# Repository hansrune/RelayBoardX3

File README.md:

# Relay board X3

Work in progress / still a prototype...

A DYI 3x relay board based on ESP32c3. This is a multi purpose board used for:

- `Garage doors` - controlling dual garage doors and control use of external switches
- `Ventilator / 1-phase small motor` 1-2-3 speed control. 

This board is tested with ESPhome and ESPEasy [firmware](#firmwares) (build instructions below), and is easily used with home automation systems that support MQTT auto discovery, the native Home Assistant API, and the many [controllers that ESPEasy supports](https://espeasy.readthedocs.io/en/latest/Controller/_Controller.html)

## Introduction

Some of the main features and benefits

- **3x galvanic isolated relays**
- **Car precense sensors**
    - Ultrasound sensor option
- **I2C support**
    - An I2C pin header with power supply is available to use with I2C sensors
    - ... or you can use the same GPIO pins for any other purpose of your choise
- **WiFi based**
    - This is almost a must have for most home automation systems
    - OTA support
    - Configuration backup, restore and bulk updates.
- **Firmware of your choise**
    - ESPEasy with Domoticz over http. Device creation uses virtual sensors
    - ESPEasy with Domotics and Home Assistant via MQTT. Device creation uses a MQTT configuration text file.
    - ESPHome to Home Assistant via MQTT and auto discovery
    - ESPHome to Domoticz via MQTT and auto discovery
    - ... and as the hardware supports using both Arduino and ESP-IF development kits, almost any other firmware can be created.
- **Seed Studio XIAO ESP32C3**
    - This device is shielded and comes with an external IPX antenna connector
    - FCC and CE regulations approved

<!--
## Setup and mounting - perhaps add later
-->

## Indicators

Each of the four valve outputs has a LED indicator at the back of the PCB

- LED D11 will indicate low level input from the flow meter
- LED D1
  - no change indicates out of power, device death/freeze or other
  - a duty cycle 1:1 will indicate a reset is ongoing
<!--
  - will blink with a duty cycle 1-4 or 4-1 to indicate valve closed or open
-->

## Implementation and design

The schematic diagram is [available here](KiCad//RelayBoardX3-schema-2.0.pdf). The [KiCad EDA](https://www.kicad.org/) project is in the [same folder](./KiCad)

### GPIO pin usage

| PIN      | Capabilty          | Function                              |
|----------|--------------------|---------------------------------------|
| GPIO2    | Acticve low output | LED D8 - not used                     |
| GPIO3    | Input with pull-up | J7 pin 2                              |
| GPIO4    | Input with pull-up | J7 pin 1                              |
| GPIO5    | Active high output | Relay 1                               |
| GPIO6    | Active high output | Relay 2                               |
| GPIO7    | I2C pulled up      | SDL                                   |
| GPIO8    | I2C pulled up      | SDA                                   |
| GPIO9    | Active low out     | LED D8 - status                       |
| GPIO10   | Active high output | Relay 3                               |
| GPIO20   | RX / 1-wire        | Serial or 1-wire sensor or ultrasound |
| GPIO21   | TX / 1-wire        | Serial or 1-wire sensor or ultrasound |

## Hardware - getting started

This project uses my [KiCad-lib-ESP32 repository](https://github.com/hansrune/KiCad-lib-ESP32.git) as a [git submodule](https://www.git-scm.com/book/en/v2/Git-Tools-Submodules). To check this out, use the following:

```bash
git clone --recurse-submodules https://github.com/hansrune/RelayBoardX4.git 
```

### Materials used

This project uses the [Seed Studio XIAO ESP32C3 RISC-V module](https://www.seeedstudio.com/Seeed-XIAO-ESP32C3-p-5431.html). This tiny device has proven to be more reliable than most ESP8266 modules used in earlier versions. This module also comes with an IPX connector for connecting an external antenna, and is delivered with a simple external antenna for good range. This device is also EMI shielded and certified.

Any available 12V DC power supply delivering 500mA or more should do for the control board. You will need to add the total power draw for the relays

There are many options and possible pinouts for DC-DC converters for the 12V to 5V conversion. A linear regulator (L7805) will need a heatsink, so a DC-DC converter is recommended.

The MOSFETs need a low Vgs trigger voltage, i.e. well under 3V on full load. I have used Si2302/N025P for the N-channel, SOT-23 package.

Resistors are 0805 size. Screw terminals are 3.5mm, which is a tight fit when ferrules are being used.

For more information, use [this KiCad BOM](KiCad/RelayBoardX3-BOM.csv)

## Hardware assembly

Soldering a prototype by hand is possible if you have a steady hand and a small solder iron tip. A microscope is recommended to inspect the solder joints properly.

Recommend to do the SMD parts first, then other components. 

### Hardware tests

You should test at least the following **before adding the ESP32 module**:

- Attach a battery and check that the valve can be operated both NO and NC
- Add power and check that 5V conversion is OK
- Apply 5V to GPIO 5, 6, and 10 in turn to check that the output works with the relay LED indicators

## Firmwares

### ESPHome

ESPHome firmware can be set up from [this ESPHome configuration repository](https://github.com/hansrune/esphome-config) using the `test_relayx3_garage.yaml` or `test_relayx3_motor.yaml` file as a template

Follow the [README](https://github.com/hansrune/esphome-config) for instructions on what you will likely want to change.

By default, MQTT auto discovery is being used. This should work out of the box with Home Assistant, Domoticz and other that support [Home Assistant MQTT Auto Discovery](https://www.home-assistant.io/integrations/mqtt/#mqtt-discovery)

#### Garage doors control

In Home Assistant, the garage door controls can look like this:

... and the closed state end stop sensors:

#### Motor control

In Home Assistant, the device has this simple selector:

### ESPEasy

ESPEasy can be used with a number of different controllers / home automation systms. A custom firmware build description is [available here](https://github.com/hansrune/ESPEasy-custom/blob/builds/custom/mega-20240822-1/README-custombuilds.md)

ESPEasy requires many settings. For configuration settings and rule files, you can upload the below sets of files. Please make sure to change name, unit number, controller IP addresses, NTP, syslog host and latitude/longitude. This configuration uses both a MQTT controller and a Domoticz controller. Change to what you need.

- For the garage control, use the files under [this page](./ESPEasy/garage)
- For the motor/ventilator control, use the files under [this page](./ESPEasy/motor/config.dat

## Wiring

### Dual garage door wiring

This dual garage door setup uses a pulse driven elevator, and has end stop switches for the closed position. There is no end stops for the open position, meaning that the open state simply reflects not closed.

A `RX-Multi` receiver is used in parallel with the relay board. This is operated by remote control units from a car.

We have outdoor push buttons to operate the garage doors. These are disabled via relay #1 when our home alarm state is away or night. The power on state is that these buttons are enabled.

### Motor control wiring

This setup is a simple 1-2-3 speed motor control for a ventilator. Can work in parallel with a 1-2-3 switch, where you will get the highest speed selected via contoller or switch.

## Licensing

This project is licensed under the [GNU General Public License v3.0](GNU-LICENSE-V3.txt) for the software, [CERN-OHL-W](OHL-LICENSE.txt) for the hardware, and [CC BY-SA](CC-BY-SA-LICENCE.txt) for the documentation and ideas.

<!-- 
| **Open Source Licenses** |                                                       |
| -------------------------|-------------------------------------------------------|
| Hardware                 | [CERN-OHL-W](OHL-LICENSE.txt)                         |
| Software                 | [GNU General Public License v3.0](GNU-LICENSE-V3.txt) |
| Documentation / idea     | [CC BY-SA](CC-BY-SA-LICENCE.txt)                      |
-->

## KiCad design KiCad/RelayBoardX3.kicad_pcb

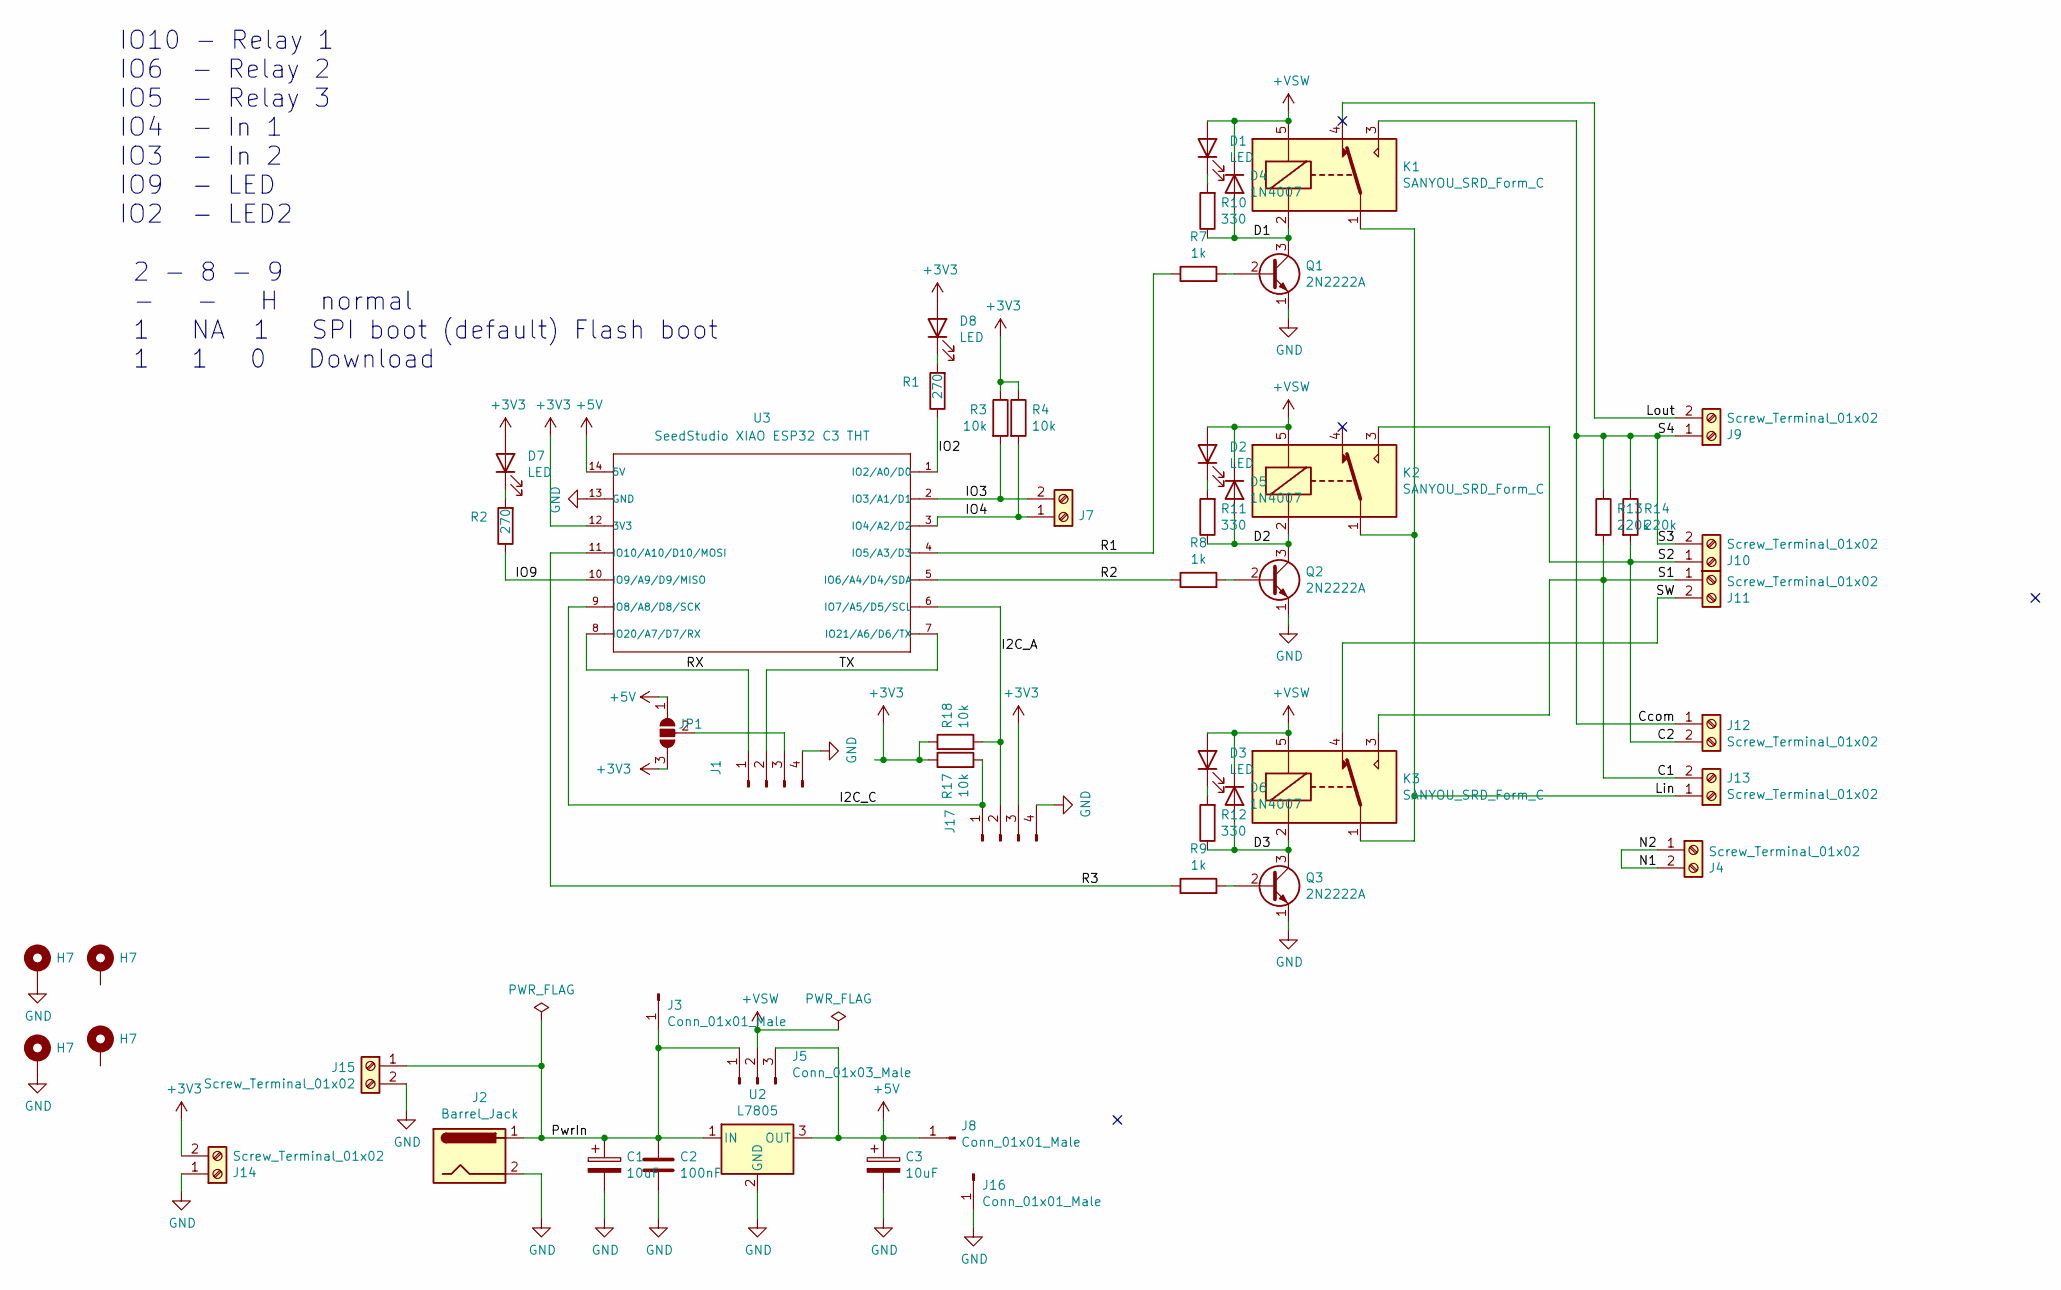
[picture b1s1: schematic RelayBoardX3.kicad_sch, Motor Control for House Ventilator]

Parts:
C1, C3: 10uF; CP_Radial_Tantal_D6.0mm_P5.00mm
C2: 100nF; C_Disc_D5.0mm_W2.5mm_P2.50mm
D1, D2, D3: LED; LED_D5.0mm_Clear
D4, D5, D6: 1N4007; D_DO-34_SOD68_P12.70mm_Horizontal
D7, D8: LED; LED_D3.0mm_Clear
H7: MountingHole_Pad; MountingHole_3.2mm_M3_ISO14580_Pad
J1, J17: Conn_01x04_Male; PinHeader_1x04_P2.54mm_Vertical
J2: Barrel_Jack; BarrelJack1
J3, J8, J16: Conn_01x01_Male; PinHeader_1x01_P2.54mm_Vertical
J4, J7, J9, J10, J11, J12, J13, J14, J15: Screw_Terminal_01x02; TerminalBlock_Phoenix_PT-1,5-2-5.0-H_1x02_P5.00mm_Horizontal
J5: Conn_01x03_Male; PinHeader_1x03_P2.54mm_Vertical
JP1: SolderJumper_3_Open; SolderJumper-3_P1.3mm_Open_Pad1.0x1.5mm_NumberLabels
K1, K2, K3: SANYOU_SRD_Form_C; Relay_SPDT_SANYOU_SRD_CutOut
Q1, Q2, Q3: 2N2222A; TO-92
R1, R2: 270; R_Axial_DIN0207_L6.3mm_D2.5mm_P2.54mm_Vertical
R3: 10k; R_Axial_DIN0207_L6.3mm_D2.5mm_P7.62mm_Horizontal
R4, R17, R18: 10k; R_Axial_DIN0207_L6.3mm_D2.5mm_P2.54mm_Vertical
R7, R8, R9: 1k; R_Axial_DIN0207_L6.3mm_D2.5mm_P2.54mm_Vertical
R10, R11, R12: 330; R_Axial_DIN0207_L6.3mm_D2.5mm_P2.54mm_Vertical
R13, R14: 220k; R_Axial_DIN0411_L9.9mm_D3.6mm_P12.70mm_Horizontal
U2: L7805; TO-220-3_Vertical
U3: SeedStudio XIAO ESP32 C3 THT; XIAO_ESP32C3_THT

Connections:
+3V3: D7.2 (A), D8.2 (A), J14.2, J17.3, JP1.3 (B), R3.1, R4.1, R17.1, R18.1, U3.12 (3V3)
+5V: C3.1, J5.3, J8.1, JP1.1 (A), U2.3 (OUT), U3.14 (5V)
+VSW: D1.2 (A), D2.2 (A), D3.2 (A), D4.1 (K), D5.1 (K), D6.1 (K), J5.2, K1.5, K2.5, K3.5
/C1: J11.1, J13.2, K3.3, R13.2
/C2: J10.1, J12.2, K2.3, R14.2
/Ccom: J9.1, J10.2, J12.1, K1.3, R13.1, R14.1
/D1: D4.2 (A), K1.2, Q1.3 (C), R10.1
/D2: D5.2 (A), K2.2, Q2.3 (C), R11.1
/D3: D6.2 (A), K3.2, Q3.3 (C), R12.1
/I2C_A: J17.2, R18.2, U3.6 (IO7/A5/D5/SCL)
/I2C_C: J17.1, R17.2, U3.9 (IO8/A8/D8/SCK)
/IO2: R1.1, U3.1 (IO2/A0/D0)
/IO3: J7.2, R3.2, U3.2 (IO3/A1/D1)
/IO4: J7.1, R4.2, U3.3 (IO4/A2/D2)
/IO9: R2.1, U3.10 (IO9/A9/D9/MISO)
/Lin: J13.1, K1.1, K2.1, K3.1
/Lout: J9.2, K1.4
/N1: J4.1, J4.2
/PwrIn: C1.1, C2.1, J2.1, J3.1, J5.1, J15.1, U2.1 (IN)
/R1: R7.1, U3.4 (IO5/A3/D3)
/R2: R8.1, U3.5 (IO6/A4/D4/SDA)
/R3: R9.1, U3.11 (IO10/A10/D10/MOSI)
/RX: J1.1, U3.8 (IO20/A7/D7/RX)
/SW: J11.2, K3.4
/TX: J1.2, U3.7 (IO21/A6/D6/TX)
GND: C1.2, C2.2, C3.2, H7.1, J1.4, J2.2, J14.1, J15.2, J16.1, J17.4, Q1.1 (E), Q2.1 (E), Q3.1 (E), U2.2 (GND), U3.13 (GND); also elsewhere on the board
unnamed: D1.1 (K), R10.2
unnamed: D2.1 (K), R11.2
unnamed: D3.1 (K), R12.2
unnamed: D7.1 (K), R2.2
unnamed: D8.1 (K), R1.2
unnamed: J1.3, JP1.2 (C)
unnamed: Q1.2 (B), R7.2
unnamed: Q2.2 (B), R8.2
unnamed: Q3.2 (B), R9.2

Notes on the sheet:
IO10 - Relay 1 IO6 - Relay 2 IO5 - Relay 3 IO4 - In 1 IO3 - In 2 IO9 - LED IO2 - LED2 2 - 8 - 9 - - H normal 1 NA 1 SPI boot (default) Flash boot 1 1 0 Download

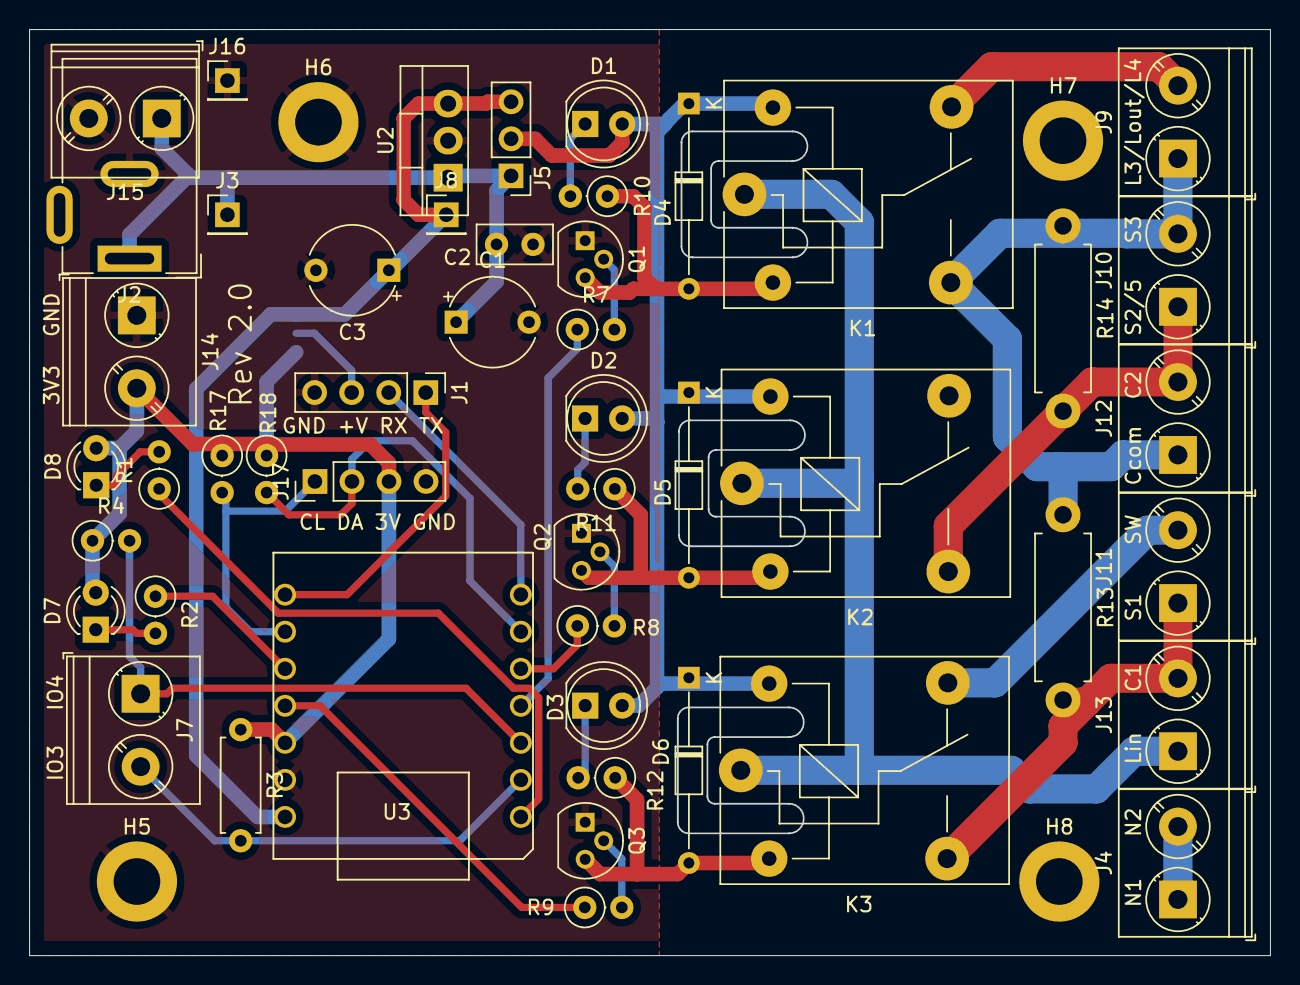
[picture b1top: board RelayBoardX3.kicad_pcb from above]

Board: 2 copper layers, 85.0 x 63.4 mm, 54 parts (1 on the bottom side), 35 nets.

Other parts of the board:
H5, H6, H8: MountingHole_Pad; MountingHole_3.2mm_M3_ISO14580_Pad

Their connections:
GND: H5.1, H6.1; also elsewhere on the board

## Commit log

2024-06-28 Version 2.0 KiCad project added
2024-09-19 New 3D model
2024-10-11 Added color specs to KiCAD schema
2024-10-11 Add wiring diagrams
2024-10-11 Add licensing files
2024-10-11 README updates
2024-10-11 Add wiring diagrams to README
2024-10-12 Home Assistant firmware for motor 1-2-3 control added
2024-10-13 Added ESPHome firmware for garage doors control
2024-10-14 Added ESPEasy configurtation files
2024-10-14 Removed misplaced section
2025-03-24 Add LICENSE overview file

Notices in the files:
KiCad/RelayBoardX3.kicad_pcb:
(C) 2023
KiCad/RelayBoardX3.kicad_sch:
Copyright - Hans Rune Bue
Hardware is licensed under CERN-OHL-W-2.0
Project documents are licensed under CC-BY-SA 2.0
